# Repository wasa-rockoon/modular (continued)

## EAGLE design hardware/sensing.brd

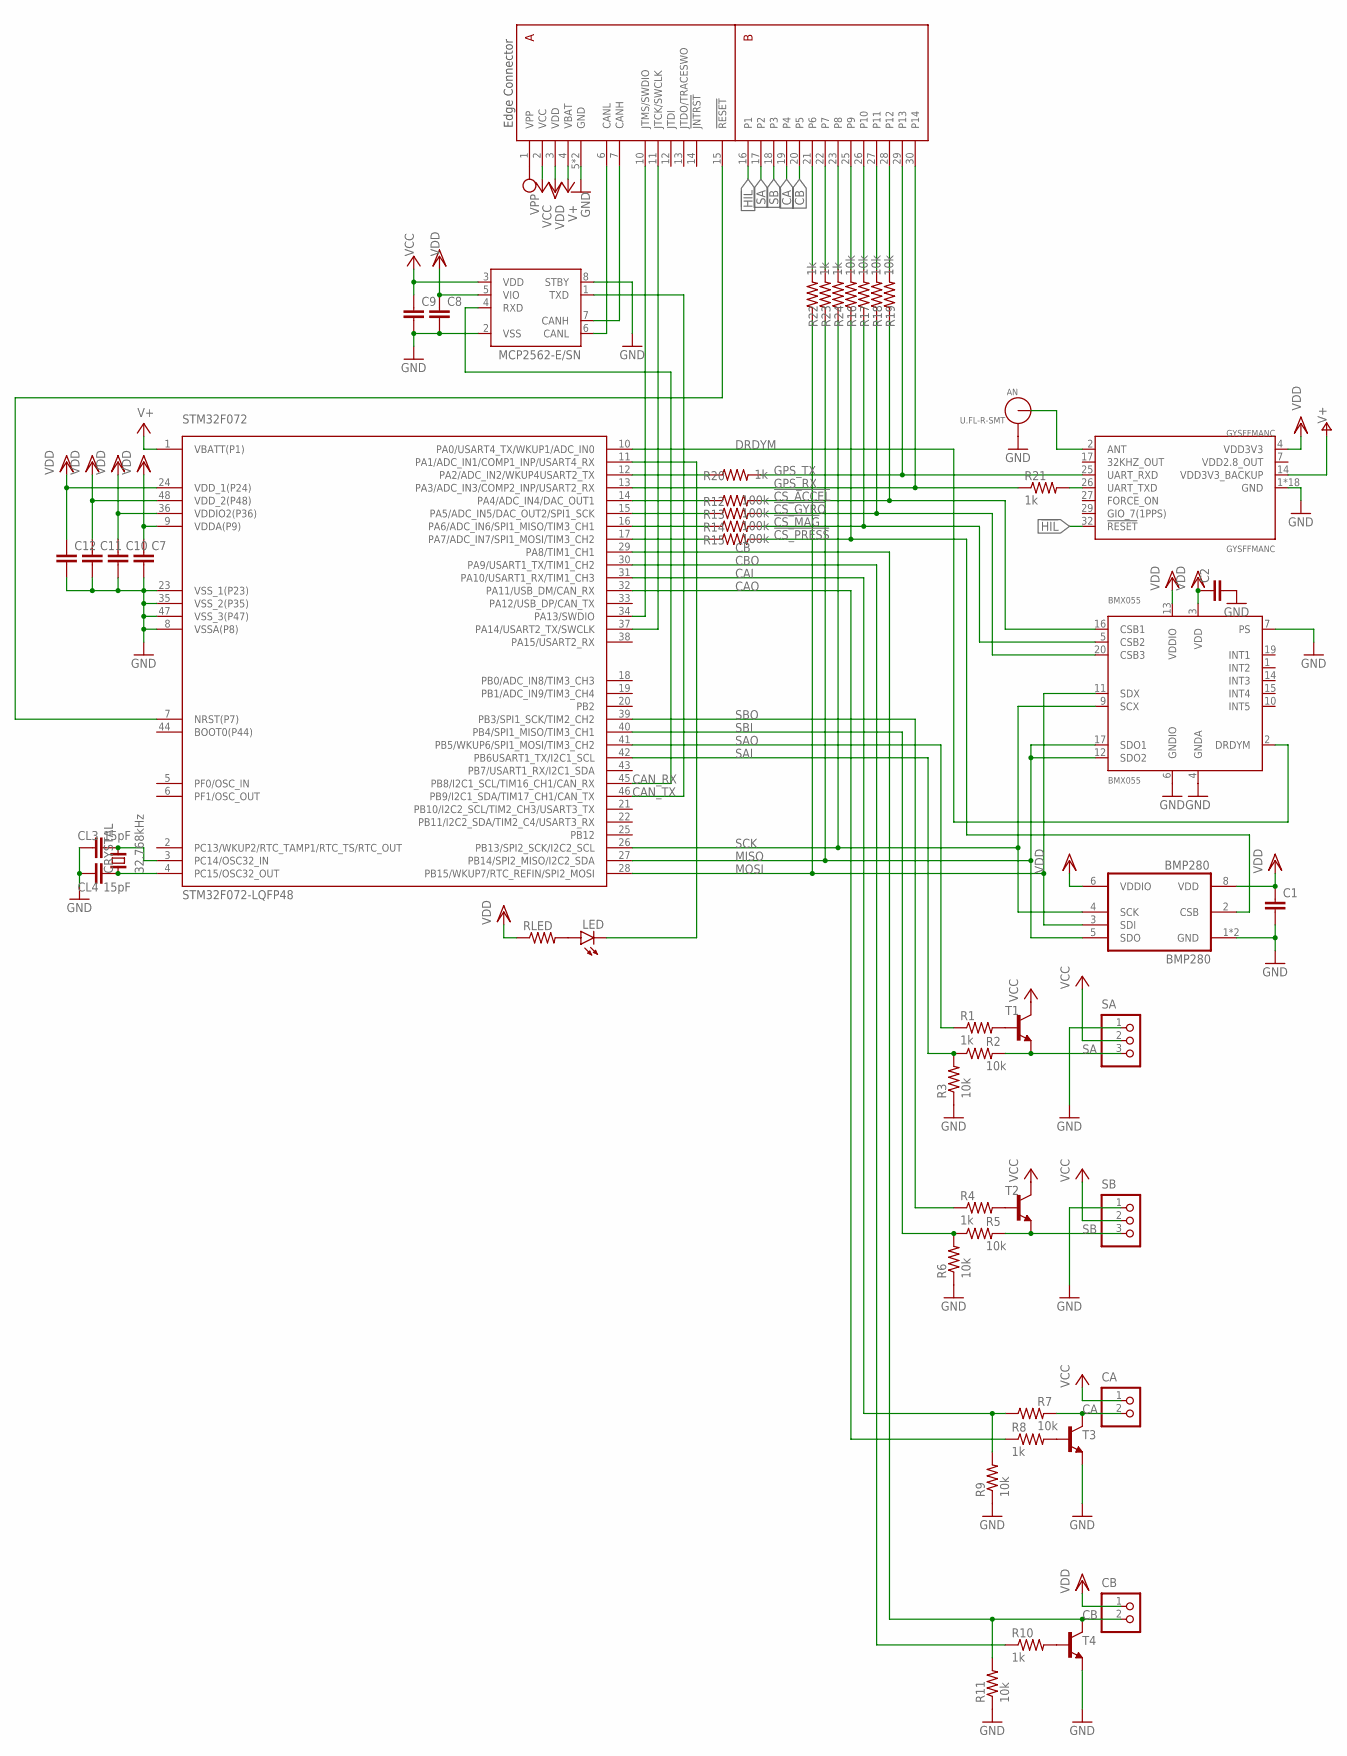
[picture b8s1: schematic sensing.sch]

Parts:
AN: U.FL-R-SMT; U.FL_SMT
BMP280: BMP280
BMX055: BMX055
C1, C2, C7, C8, C9, C10, C11, C12: C-EUC0603K; C0603K
CA: S2B-PH-K-S
CB: S2B-PH-K-S
CL3, CL4: 15pF; C0603K
CRYSTAL: 32.768kHz; FC-255
GYSFFMANC: GYSFFMANC
LED: LEDCHIP-LED0603; CHIP-LED0603
MCP2562: MCP2562-E/SN; SOIC127P600X175-8N
R1, R4, R8, R10, R20, R21, R22, R23, R24: 1k; R0603
R2, R3, R5, R6, R7, R9, R11, R16, R17, R18, R19: 10k; R0603
R12, R13, R14, R15: 100k; R0603
RLED: R-US_R0603; R0603
SA: S3B-PH-K-S
SB: S3B-PH-K-S
STM32F072: STM32F072-LQFP48; LQFP48
T1, T2, T3, T4: BC817-NPN-SOT23-BEC; SOT23-BEC
U$2: EDGE30

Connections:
!CS_ACCEL!: BMX055.16 (CSB1), R12.2, R19.1
!CS_GYRO!: BMX055.20 (CSB3), R13.2, R18.1
!CS_MAG!: BMX055.5 (CSB2), R14.2, R17.1
!CS_PRESS!: BMP280.2 (CSB), R15.2, R16.1
!HIL!: GYSFFMANC.32 (!RESET!), U$2.16 (P1)
CA: CA.2, R7.2, T3.C, U$2.19 (P4)
CAI: R7.1, R9.2, STM32F072.31 (PA10/USART1_RX/TIM1_CH3)
CANH1: MCP2562.7 (CANH), U$2.7 (CANH)
CANL1: MCP2562.6 (CANL), U$2.6 (CANL)
CAN_RX: MCP2562.4 (RXD), STM32F072.45 (PB8/I2C1_SCL/TIM16_CH1/CAN_RX)
CAN_TX: MCP2562.1 (TXD), STM32F072.46 (PB9/I2C1_SDA/TIM17_CH1/CAN_TX)
CAO: R8.1, STM32F072.32 (PA11/USB_DM/CAN_RX)
CB: CB.2, R11.2, STM32F072.29 (PA8/TIM1_CH1), T4.C, U$2.20 (P5)
CBO: R10.1, STM32F072.30 (PA9/USART1_TX/TIM1_CH2)
DRDYM: BMX055.2 (DRDYM), STM32F072.10 (PA0/USART4_TX/WKUP1/ADC_IN0)
GND: AN.GND1, AN.GND2, BMP280.1 (GND), BMP280.7 (GND), BMX055.4 (GNDA), BMX055.6 (GNDIO), BMX055.7 (PS), C1.2, C2.2, C7.2, C8.2, C9.2, C10.2, C11.2, C12.2, CL3.1, CL4.1, GYSFFMANC.1 (GND), GYSFFMANC.3 (GND), GYSFFMANC.8 (GND), GYSFFMANC.10 (GND), GYSFFMANC.12 (GND), GYSFFMANC.22 (GND), GYSFFMANC.33 (GND), GYSFFMANC.36 (GND), GYSFFMANC.37 (GND), GYSFFMANC.38 (GND), GYSFFMANC.39 (GND), GYSFFMANC.40 (GND), GYSFFMANC.41 (GND), GYSFFMANC.42 (GND), GYSFFMANC.43 (GND), GYSFFMANC.44 (GND), GYSFFMANC.45 (GND), GYSFFMANC.46 (GND), MCP2562.2 (VSS), MCP2562.8 (STBY), R3.1, R6.1, R9.1, R11.1, SA.1, SB.1, STM32F072.8 (VSSA(P8)), STM32F072.23 (VSS_1(P23)), STM32F072.35 (VSS_2(P35)), STM32F072.47 (VSS_3(P47)), T3.E, T4.E, U$2.5 (GND), U$2.8 (GND)
GPS_RX: R21.1, STM32F072.13 (PA3/ADC_IN3/COMP2_INP/USART2_RX), U$2.30 (P14)
GPS_TX: GYSFFMANC.25 (UART_RXD), R20.2, U$2.29 (P13)
MISO: BMP280.5 (SDO), BMX055.12 (SDO2), BMX055.17 (SDO1), R23.1, STM32F072.27 (PB14/SPI2_MISO/I2C2_SDA)
MOSI: BMP280.3 (SDI), BMX055.11 (SDX), R22.1, STM32F072.28 (PB15/WKUP7/RTC_REFIN/SPI2_MOSI)
unnamed: AN.SIG (ANT), GYSFFMANC.2 (ANT)
unnamed: R12.1, STM32F072.14 (PA4/ADC_IN4/DAC_OUT1)
unnamed: R1.2, T1.B
unnamed: R4.2, T2.B
unnamed: R13.1, STM32F072.15 (PA5/ADC_IN5/DAC_OUT2/SPI1_SCK)
unnamed: R14.1, STM32F072.16 (PA6/ADC_IN6/SPI1_MISO/TIM3_CH1)
unnamed: R15.1, STM32F072.17 (PA7/ADC_IN7/SPI1_MOSI/TIM3_CH2)
unnamed: R20.1, STM32F072.12 (PA2/ADC_IN2/WKUP4USART2_TX)
unnamed: GYSFFMANC.26 (UART_TXD), R21.2
unnamed: R8.2, T3.B
unnamed: R10.2, T4.B
unnamed: R24.2, U$2.23 (P8)
unnamed: R23.2, U$2.22 (P7)
unnamed: R22.2, U$2.21 (P6)
unnamed: R19.2, U$2.28 (P12)
unnamed: R18.2, U$2.27 (P11)
unnamed: R17.2, U$2.26 (P10)
unnamed: R16.2, U$2.25 (P9)
unnamed: LED.C, STM32F072.11 (PA1/ADC_IN1/COMP1_INP/USART4_RX)
unnamed: CL4.2, CRYSTAL.1, STM32F072.4 (PC15/OSC32_OUT)
unnamed: CL3.2, CRYSTAL.2, STM32F072.3 (PC14/OSC32_IN)
unnamed: LED.A, RLED.2
NRST1: STM32F072.7 (NRST(P7)), U$2.15 (!RESET!)
SA: R2.2, SA.3, T1.E, U$2.17 (P2)
SAI: R2.1, R3.2, STM32F072.42 (PB6USART1_TX/I2C1_SCL)
SAO: R1.1, STM32F072.41 (PB5/WKUP6/SPI1_MOSI/TIM3_CH2)
SB: R5.2, SB.3, T2.E, U$2.18 (P3)
SBI: R5.1, R6.2, STM32F072.40 (PB4/SPI1_MISO/TIM3_CH1)
SBO: R4.1, STM32F072.39 (PB3/SPI1_SCK/TIM2_CH2)
SCK: BMP280.4 (SCK), BMX055.9 (SCX), R24.1, STM32F072.26 (PB13/SPI2_SCK/I2C2_SCL)
SWCLK1: STM32F072.37 (PA14/USART2_TX/SWCLK), U$2.11 (JTCK/SWCLK)
SWDIO1: STM32F072.34 (PA13/SWDIO), U$2.10 (JTMS/SWDIO)
VBAT: GYSFFMANC.14 (VDD3V3_BACKUP), STM32F072.1 (VBATT(P1)), U$2.4 (VBAT)
VCC: C9.1, CA.1, MCP2562.3 (VDD), SA.2, SB.2, T1.C, T2.C, U$2.2 (VCC)
VDD: BMP280.6 (VDDIO), BMP280.8 (VDD), BMX055.3 (VDD), BMX055.13 (VDDIO), C1.1, C2.1, C7.1, C8.1, C10.1, C11.1, C12.1, CB.1, GYSFFMANC.4 (VDD3V3), MCP2562.5 (VIO), RLED.1, STM32F072.9 (VDDA(P9)), STM32F072.24 (VDD_1(P24)), STM32F072.36 (VDDIO2(P36)), STM32F072.48 (VDD_2(P48)), U$2.3 (VDD)
VDD2.8_OUT: GYSFFMANC.7 (VDD2.8_OUT)
VPP: U$2.1 (VPP)

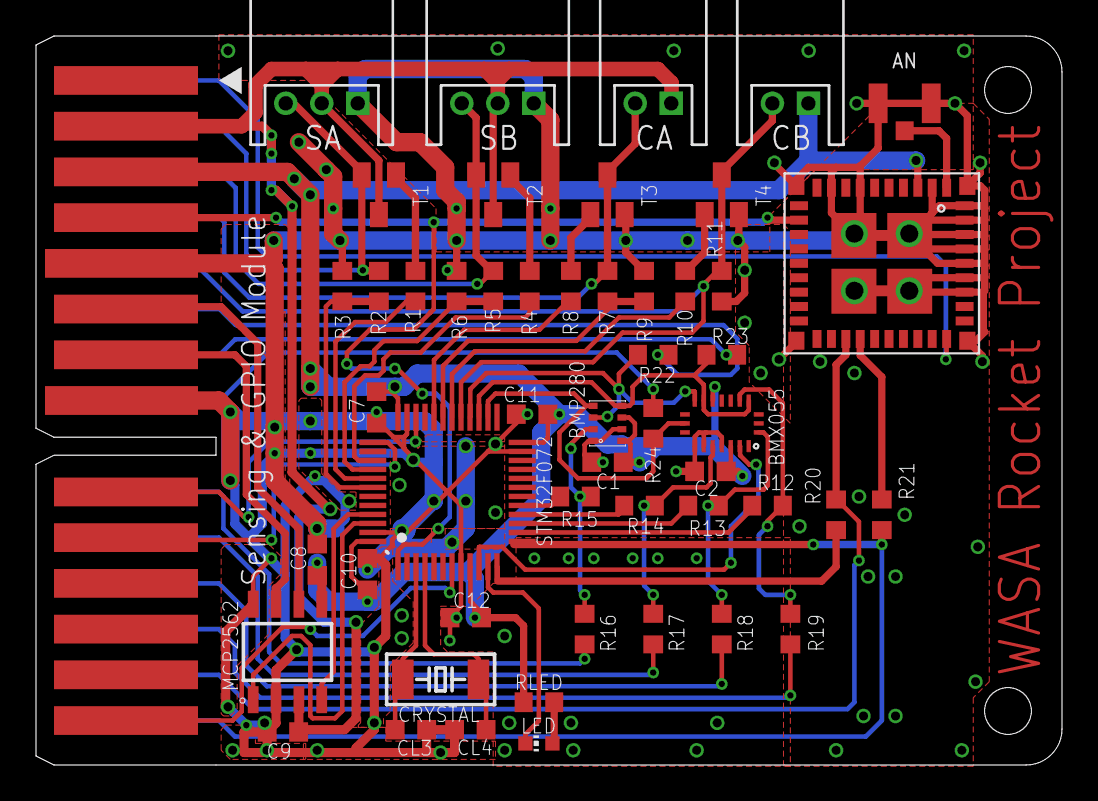
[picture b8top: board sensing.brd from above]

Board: 2 copper layers, 57.0 x 40.5 mm, 52 parts (0 on the bottom side), 55 nets.

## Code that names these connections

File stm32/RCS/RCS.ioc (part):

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Mcu.Name=STM32F042C(4-6)Tx
Mcu.Package=LQFP48
Mcu.UserName=STM32F042C6Tx
PA0.GPIOParameters=GPIO_Label
PA0.GPIO_Label=LED_ERROR
PA0.Signal=GPIO_Output
PA1.GPIOParameters=PinState,GPIO_PuPd,GPIO_Label,GPIO_ModeDefaultOutputPP
PA1.GPIO_Label=LED_A
PA1.GPIO_ModeDefaultOutputPP=GPIO_MODE_OUTPUT_PP
PA1.GPIO_PuPd=GPIO_NOPULL
PA1.PinState=GPIO_PIN_RESET
PA1.Signal=GPIO_Output
PA13.Mode=Serial_Wire
PA13.Signal=SYS_SWDIO
PA14.Mode=Serial_Wire
PA14.Signal=SYS_SWCLK
PA2.GPIOParameters=GPIO_Label
PA2.GPIO_Label=LED_B
PA2.Signal=GPIO_Output
PA3.GPIOParameters=GPIO_Label
PA3.GPIO_Label=LED_C
PA3.Signal=GPIO_Output
PA4.GPIOParameters=GPIO_Label
PA4.GPIO_Label=LED_D
PA4.Signal=S_TIM14_CH1
PA6.GPIOParameters=GPIO_Label
PA6.GPIO_Label=X_DATA
PA6.Signal=GPIO_Input
PA7.GPIOParameters=GPIO_Label
PA7.GPIO_Label=X_SCK
PA7.Signal=GPIO_Output
PA8.GPIOParameters=GPIO_Label
PA8.GPIO_Label=VALVE_A
PA8.Signal=GPIO_Output
PB0.GPIOParameters=GPIO_Label
PB0.GPIO_Label=PRESSURE
PB0.Mode=IN8
PB0.Signal=ADC_IN8
PB1.GPIOParameters=GPIO_Label
PB1.GPIO_Label=POWER_FB
PB1.Mode=IN9
PB1.Signal=ADC_IN9
PB10.GPIOParameters=GPIO_Label
PB10.GPIO_Label=Y_DATA
PB10.Signal=GPIO_Input
PB11.GPIOParameters=GPIO_Label
PB11.GPIO_Label=Y_SCK
PB11.Signal=GPIO_Output
PB12.GPIOParameters=GPIO_Label
PB12.GPIO_Label=POWER_ON
PB12.Signal=GPIO_Output
PB13.GPIOParameters=GPIO_Label
PB13.GPIO_Label=VALVE_D
PB13.Signal=GPIO_Output
PB14.GPIOParameters=GPIO_Label
PB14.GPIO_Label=VALVE_C
PB14.Signal=GPIO_Output
PB15.GPIOParameters=GPIO_Label
PB15.GPIO_Label=VALVE_B
PB15.Signal=GPIO_Output
PB8.GPIOParameters=GPIO_PuPd
PB8.GPIO_PuPd=GPIO_PULLUP
PB8.Mode=CAN_Activate
PB8.Signal=CAN_RX
PB9.Mode=CAN_Activate
PB9.Signal=CAN_TX
board=custom

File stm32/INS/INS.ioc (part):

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Mcu.Name=STM32L431C(B-C)Tx
Mcu.Package=LQFP48
Mcu.UserName=STM32L431CCTx
PA0.GPIOParameters=GPIO_Label
PA0.GPIO_Label=LED_ERROR
PA0.Signal=GPIO_Output
PA1.GPIOParameters=GPIO_Label
PA1.GPIO_Label=LED_STATUS
PA1.Signal=GPIO_Output
PA10.GPIOParameters=GPIO_Label
PA10.GPIO_Label=GPS_RX
PA10.Mode=Asynchronous
PA10.Signal=USART1_RX
PA11.GPIOParameters=GPIO_Label
PA11.GPIO_Label=TEMP_LOW
PA11.Signal=GPIO_Output
PA12.GPIOParameters=GPIO_Label
PA12.GPIO_Label=TEMP_HIGH
PA12.Signal=GPIO_Output
PA13\ (JTMS-SWDIO).Signal=SYS_JTMS-SWDIO
PA14\ (JTCK-SWCLK).Signal=SYS_JTCK-SWCLK
PA2.Mode=Asynchronous
PA2.Signal=USART2_TX
PA3.Mode=Asynchronous
PA3.Signal=USART2_RX
PA8.GPIOParameters=GPIO_Label
PA8.GPIO_Label=GPS_RESET
PA8.Signal=GPIO_Output
PA9.GPIOParameters=GPIO_Label
PA9.GPIO_Label=GPS_TX
PA9.Mode=Asynchronous
PA9.Signal=USART1_TX
PB1.GPIOParameters=GPIO_Label
PB1.GPIO_Label=TEMP
PB1.Signal=ADCx_IN16
PB10.Mode=I2C
PB10.Signal=I2C2_SCL
PB11.Mode=I2C
PB11.Signal=I2C2_SDA
PB15.GPIOParameters=GPIO_Label
PB15.GPIO_Label=GPS_1PPS
PB15.Signal=GPIO_Input
PB2.GPIOParameters=GPIO_Label
PB2.GPIO_Label=BNO_RESET
PB2.Signal=GPIO_Output
PB6.Mode=I2C
PB6.Signal=I2C1_SCL
PB7.Mode=I2C
PB7.Signal=I2C1_SDA
PB8.Mode=CAN_Activate
PB8.Signal=CAN1_RX
PB9.Mode=CAN_Activate
PB9.Signal=CAN1_TX
PC14-OSC32_IN\ (PC14).Mode=LSE-External-Oscillator
PC14-OSC32_IN\ (PC14).Signal=RCC_OSC32_IN
PC15-OSC32_OUT\ (PC15).Mode=LSE-External-Oscillator
PC15-OSC32_OUT\ (PC15).Signal=RCC_OSC32_OUT
RCC.HSE_VALUE=8000000
RCC.SYSCLKFreq_VALUE=80000000
RCC.SYSCLKSource=RCC_SYSCLKSOURCE_PLLCLK
board=custom

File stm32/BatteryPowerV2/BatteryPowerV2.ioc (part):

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Mcu.Name=STM32F042C(4-6)Tx
Mcu.Package=LQFP48
Mcu.UserName=STM32F042C6Tx
PA0.GPIOParameters=GPIO_Label
PA0.GPIO_Label=LED_ERROR
PA0.Signal=GPIO_Output
PA1.GPIOParameters=GPIO_Label
PA1.GPIO_Label=LED_STATUS
PA1.Signal=GPIO_Output
PA10.GPIOParameters=GPIO_Label
PA10.GPIO_Label=SUPPLY_CON
PA10.Signal=GPIO_Input
PA11.GPIOParameters=GPIO_Label
PA11.GPIO_Label=SUPPLY_3V3
PA11.Signal=GPIO_Output
PA12.GPIOParameters=GPIO_Label
PA12.GPIO_Label=SUPPLY_5V
PA12.Signal=GPIO_Output
PA13.Mode=Serial_Wire
PA13.Signal=SYS_SWDIO
PA14.Mode=Serial_Wire
PA14.Signal=SYS_SWCLK
PA2.GPIOParameters=GPIO_Label
PA2.GPIO_Label=TEMP
PA2.Mode=IN2
PA2.Signal=ADC_IN2
PA3.GPIOParameters=GPIO_Label
PA3.GPIO_Label=VDD_V
PA3.Mode=IN3
PA3.Signal=ADC_IN3
PA4.GPIOParameters=GPIO_Label
PA4.GPIO_Label=VDD_I
PA4.Mode=IN4
PA4.Signal=ADC_IN4
PA5.GPIOParameters=GPIO_Label
PA5.GPIO_Label=VCC_V
PA5.Mode=IN5
PA5.Signal=ADC_IN5
PA6.GPIOParameters=GPIO_Label
PA6.GPIO_Label=VCC_I
PA6.Mode=IN6
PA6.Signal=ADC_IN6
PA7.GPIOParameters=GPIO_Label
PA7.GPIO_Label=BAT2_V
PA7.Mode=IN7
PA7.Signal=ADC_IN7
PA9.GPIOParameters=GPIO_Label
PA9.GPIO_Label=HEATER
PA9.Signal=GPIO_Output
PB0.GPIOParameters=GPIO_Label
PB0.GPIO_Label=BAT1_V
PB0.Mode=IN8
PB0.Signal=ADC_IN8
PB1.GPIOParameters=GPIO_Label
PB1.GPIO_Label=VPP_V
PB1.Mode=IN9
PB1.Signal=ADC_IN9
PB8.Mode=CAN_Activate
PB8.Signal=CAN_RX
PB9.Mode=CAN_Activate
PB9.Signal=CAN_TX
PC14OSC32_IN.Mode=LSE-External-Oscillator
PC14OSC32_IN.Signal=RCC_OSC32_IN
PC15OSC32_OUT.Mode=LSE-External-Oscillator
PC15OSC32_OUT.Signal=RCC_OSC32_OUT
RCC.SYSCLKFreq_VALUE=48000000
RCC.SYSCLKSource=RCC_SYSCLKSOURCE_HSI48
board=custom

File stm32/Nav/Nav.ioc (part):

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Mcu.Name=STM32G431C(6-8-B)Tx
Mcu.Package=LQFP48
Mcu.UserName=STM32G431C6Tx
PA0.GPIOParameters=GPIO_Label
PA0.GPIO_Label=DRDYM
PA0.Signal=GPIO_Input
PA1.GPIOParameters=PinState,GPIO_Label
PA1.GPIO_Label=LED
PA1.PinState=GPIO_PIN_SET
PA1.Signal=GPIO_Output
PA11.GPIOParameters=GPIO_Label
PA11.GPIO_Label=CAN_RX
PA11.Mode=FDCAN_Activate
PA11.Signal=FDCAN1_RX
PA12.GPIOParameters=GPIO_Label
PA12.GPIO_Label=CAN_TX
PA12.Mode=FDCAN_Activate
PA12.Signal=FDCAN1_TX
PA13.Mode=Serial_Wire
PA13.Signal=SYS_JTMS-SWDIO
PA14.Mode=Serial_Wire
PA14.Signal=SYS_JTCK-SWCLK
PA2.GPIOParameters=GPIO_Label
PA2.GPIO_Label=GPS_TX
PA2.Mode=Asynchronous
PA2.Signal=USART2_TX
PA3.GPIOParameters=GPIO_Label
PA3.GPIO_Label=GPS_RX
PA3.Mode=Asynchronous
PA3.Signal=USART2_RX
PA4.GPIOParameters=GPIO_Speed,PinState,GPIO_Label
PA4.GPIO_Label=CS_ACCL
PA4.GPIO_Speed=GPIO_SPEED_FREQ_HIGH
PA4.PinState=GPIO_PIN_SET
PA4.Signal=GPIO_Output
PA5.GPIOParameters=GPIO_Speed,PinState,GPIO_Label
PA5.GPIO_Label=CS_MAG
PA5.GPIO_Speed=GPIO_SPEED_FREQ_HIGH
PA5.PinState=GPIO_PIN_SET
PA5.Signal=GPIO_Output
PA6.GPIOParameters=GPIO_Speed,PinState,GPIO_Label
PA6.GPIO_Label=CS_GYRO
PA6.GPIO_Speed=GPIO_SPEED_FREQ_HIGH
PA6.PinState=GPIO_PIN_SET
PA6.Signal=GPIO_Output
PA7.GPIOParameters=GPIO_Speed,PinState,GPIO_Label
PA7.GPIO_Label=CS_PRES
PA7.GPIO_Speed=GPIO_SPEED_FREQ_HIGH
PA7.PinState=GPIO_PIN_SET
PA7.Signal=GPIO_Output
PA8.GPIOParameters=GPIO_Label
PA8.GPIO_Label=I2C_SDA
PA8.Mode=I2C
PA8.Signal=I2C2_SDA
PA9.GPIOParameters=GPIO_Label
PA9.GPIO_Label=I2C_SCL
PA9.Mode=I2C
PA9.Signal=I2C2_SCL
PB13.GPIOParameters=GPIO_Speed,GPIO_Label
PB13.GPIO_Label=SPI_SCK
PB13.GPIO_Speed=GPIO_SPEED_FREQ_HIGH
PB13.Mode=Full_Duplex_Master
PB13.Signal=SPI2_SCK
PB14.GPIOParameters=GPIO_Speed,GPIO_Label
PB14.GPIO_Label=SPI_MISO
PB14.GPIO_Speed=GPIO_SPEED_FREQ_HIGH
PB14.Mode=Full_Duplex_Master
PB14.Signal=SPI2_MISO
PB15.GPIOParameters=GPIO_Speed,GPIO_Label
PB15.GPIO_Label=SPI_MOSI
PB15.GPIO_Speed=GPIO_SPEED_FREQ_HIGH
PB15.Mode=Full_Duplex_Master
PB15.Signal=SPI2_MOSI
RCC.HSE_VALUE=8000000
RCC.SYSCLKFreq_VALUE=150000000
RCC.SYSCLKSource=RCC_SYSCLKSOURCE_PLLCLK
board=custom

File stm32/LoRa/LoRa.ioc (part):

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Mcu.Name=STM32F042C(4-6)Tx
Mcu.Package=LQFP48
Mcu.UserName=STM32F042C6Tx
PA0.GPIOParameters=GPIO_Label
PA0.GPIO_Label=LED_ERROR
PA0.Signal=GPIO_Output
PA1.GPIOParameters=GPIO_Label
PA1.GPIO_Label=LED_STATUS1
PA1.Signal=GPIO_Output
PA10.GPIOParameters=GPIO_ModeDefaultPP,GPIO_Speed,GPIO_PuPd
PA10.GPIO_ModeDefaultPP=GPIO_MODE_AF_PP
PA10.GPIO_PuPd=GPIO_NOPULL
PA10.GPIO_Speed=GPIO_SPEED_FREQ_HIGH
PA10.Mode=Asynchronous
PA10.Signal=USART1_RX
PA11.GPIOParameters=GPIO_Label
PA11.GPIO_Label=LORA1_M1
PA11.Signal=GPIO_Output
PA12.GPIOParameters=GPIO_Label
PA12.GPIO_Label=LORA1_M0
PA12.Signal=GPIO_Output
PA13.Mode=Serial_Wire
PA13.Signal=SYS_SWDIO
PA14.Mode=Serial_Wire
PA14.Signal=SYS_SWCLK
PA2.GPIOParameters=GPIO_ModeDefaultPP,GPIO_Speed,GPIO_PuPd
PA2.GPIO_ModeDefaultPP=GPIO_MODE_AF_PP
PA2.GPIO_PuPd=GPIO_NOPULL
PA2.GPIO_Speed=GPIO_SPEED_FREQ_HIGH
PA2.Mode=Asynchronous
PA2.Signal=USART2_TX
PA3.GPIOParameters=GPIO_ModeDefaultPP,GPIO_Speed,GPIO_PuPd
PA3.GPIO_ModeDefaultPP=GPIO_MODE_AF_PP
PA3.GPIO_PuPd=GPIO_NOPULL
PA3.GPIO_Speed=GPIO_SPEED_FREQ_HIGH
PA3.Mode=Asynchronous
PA3.Signal=USART2_RX
PA4.GPIOParameters=GPIO_Label
PA4.GPIO_Label=LED_STATUS2
PA4.Signal=GPIO_Output
PA5.GPIOParameters=GPIO_PuPd,GPIO_Label
PA5.GPIO_Label=LORA2_AUX
PA5.GPIO_PuPd=GPIO_PULLUP
PA5.Signal=GPIO_Input
PA6.GPIOParameters=GPIO_Label
PA6.GPIO_Label=LORA2_M1
PA6.Signal=GPIO_Output
PA7.GPIOParameters=GPIO_Label
PA7.GPIO_Label=LORA2_M0
PA7.Signal=GPIO_Output
PA9.GPIOParameters=GPIO_ModeDefaultPP,GPIO_Speed,GPIO_PuPd
PA9.GPIO_ModeDefaultPP=GPIO_MODE_AF_PP
PA9.GPIO_PuPd=GPIO_NOPULL
PA9.GPIO_Speed=GPIO_SPEED_FREQ_HIGH
PA9.Mode=Asynchronous
PA9.Signal=USART1_TX
PB11.GPIOParameters=GPIO_PuPd,GPIO_Label
PB11.GPIO_Label=LORA1_AUX
PB11.GPIO_PuPd=GPIO_PULLUP
PB11.Signal=GPIO_Input
PB8.GPIOParameters=GPIO_PuPd
PB8.GPIO_PuPd=GPIO_PULLUP
PB8.Mode=CAN_Activate
PB8.Signal=CAN_RX
PB9.Mode=CAN_Activate
PB9.Signal=CAN_TX
PC14OSC32_IN.Mode=LSE-External-Oscillator
PC14OSC32_IN.Signal=RCC_OSC32_IN
PC15OSC32_OUT.Mode=LSE-External-Oscillator
PC15OSC32_OUT.Signal=RCC_OSC32_OUT
RCC.SYSCLKFreq_VALUE=48000000
RCC.SYSCLKSource=RCC_SYSCLKSOURCE_HSI48
board=custom

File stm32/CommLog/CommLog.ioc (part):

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Mcu.Name=STM32F042C(4-6)Tx
Mcu.Package=LQFP48
Mcu.UserName=STM32F042C6Tx
PA1.GPIOParameters=GPIO_Label
PA1.GPIO_Label=LED
PA1.Signal=GPIO_Output
PA11.GPIOParameters=PinState,GPIO_PuPd,GPIO_Label,GPIO_ModeDefaultOutputPP
PA11.GPIO_Label=TWE_NRST
PA11.GPIO_ModeDefaultOutputPP=GPIO_MODE_OUTPUT_OD
PA11.GPIO_PuPd=GPIO_PULLUP
PA11.PinState=GPIO_PIN_SET
PA11.Signal=GPIO_Output
PA13.Mode=Serial_Wire
PA13.Signal=SYS_SWDIO
PA14.Mode=Serial_Wire
PA14.Signal=SYS_SWCLK
PA15.GPIOParameters=GPIO_ModeDefaultPP,GPIO_PuPd,GPIO_Label
PA15.GPIO_Label=LORA_RTX
PA15.GPIO_ModeDefaultPP=GPIO_MODE_AF_OD
PA15.GPIO_PuPd=GPIO_PULLUP
PA15.Mode=Asynchronous
PA15.Signal=USART2_RX
PA2.GPIOParameters=GPIO_ModeDefaultPP,GPIO_PuPd,GPIO_Label
PA2.GPIO_Label=LORA_TRX
PA2.GPIO_ModeDefaultPP=GPIO_MODE_AF_OD
PA2.GPIO_PuPd=GPIO_PULLUP
PA2.Mode=Asynchronous
PA2.Signal=USART2_TX
PA3.GPIOParameters=GPIO_PuPd,GPIO_Label
PA3.GPIO_Label=SD_NSW
PA3.GPIO_PuPd=GPIO_PULLUP
PA3.Signal=GPIO_Input
PA8.GPIOParameters=PinState,GPIO_PuPd,GPIO_Label,GPIO_ModeDefaultOutputPP
PA8.GPIO_Label=LORA_NSLEEP
PA8.GPIO_ModeDefaultOutputPP=GPIO_MODE_OUTPUT_OD
PA8.GPIO_PuPd=GPIO_PULLUP
PA8.PinState=GPIO_PIN_SET
PA8.Signal=GPIO_Output
PB13.GPIOParameters=GPIO_Label
PB13.GPIO_Label=SD_SCK
PB13.Mode=Full_Duplex_Master
PB13.Signal=SPI2_SCK
PB14.GPIOParameters=GPIO_PuPd,GPIO_Label
PB14.GPIO_Label=SD_MISO
PB14.GPIO_PuPd=GPIO_PULLUP
PB14.Mode=Full_Duplex_Master
PB14.Signal=SPI2_MISO
PB15.GPIOParameters=GPIO_PuPd,GPIO_Label
PB15.GPIO_Label=SD_MOSI
PB15.GPIO_PuPd=GPIO_PULLUP
PB15.Mode=Full_Duplex_Master
PB15.Signal=SPI2_MOSI
PB3.GPIOParameters=PinState,GPIO_PuPd,GPIO_Label,GPIO_ModeDefaultOutputPP
PB3.GPIO_Label=TWE_NSLEEP
PB3.GPIO_ModeDefaultOutputPP=GPIO_MODE_OUTPUT_OD
PB3.GPIO_PuPd=GPIO_PULLUP
PB3.PinState=GPIO_PIN_SET
PB3.Signal=GPIO_Output
PB4.GPIOParameters=PinState,GPIO_PuPd,GPIO_Label,GPIO_ModeDefaultOutputPP
PB4.GPIO_Label=TWE_NPGM
PB4.GPIO_ModeDefaultOutputPP=GPIO_MODE_OUTPUT_OD
PB4.GPIO_PuPd=GPIO_PULLUP
PB4.PinState=GPIO_PIN_SET
PB4.Signal=GPIO_Output
PB6.GPIOParameters=GPIO_ModeDefaultPP,GPIO_PuPd,GPIO_Label
PB6.GPIO_Label=TWE_TRX
PB6.GPIO_ModeDefaultPP=GPIO_MODE_AF_OD
PB6.GPIO_PuPd=GPIO_PULLUP
PB6.Mode=Asynchronous
PB6.Signal=USART1_TX
PB7.GPIOParameters=GPIO_ModeDefaultPP,GPIO_PuPd,GPIO_Label
PB7.GPIO_Label=TWE_RTX
PB7.GPIO_ModeDefaultPP=GPIO_MODE_AF_OD
PB7.GPIO_PuPd=GPIO_PULLUP
PB7.Mode=Asynchronous
PB7.Signal=USART1_RX
PB8.GPIOParameters=GPIO_PuPd
PB8.GPIO_PuPd=GPIO_PULLUP
PB8.Mode=CAN_Activate
PB8.Signal=CAN_RX
PB9.Mode=CAN_Activate
PB9.Signal=CAN_TX
PC13.GPIOParameters=PinState,GPIO_PuPd,GPIO_Label,GPIO_ModeDefaultOutputPP
PC13.GPIO_Label=LORA_NRST
PC13.GPIO_ModeDefaultOutputPP=GPIO_MODE_OUTPUT_OD
PC13.GPIO_PuPd=GPIO_PULLUP
PC13.PinState=GPIO_PIN_SET
PC13.Signal=GPIO_Output
RCC.SYSCLKFreq_VALUE=48000000
RCC.SYSCLKSource=RCC_SYSCLKSOURCE_HSI48
board=custom

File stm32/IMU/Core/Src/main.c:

/* USER CODE BEGIN Header */
/**
  ******************************************************************************
  * @file           : main.c
  * @brief          : Main program body
  ******************************************************************************
  * @attention
  *
  * Copyright (c) 2022 STMicroelectronics.
  * All rights reserved.
  *
  * This software is licensed under terms that can be found in the LICENSE file
  * in the root directory of this software component.
  * If no LICENSE file comes with this software, it is provided AS-IS.
  *
  ******************************************************************************
  */
/* USER CODE END Header */
/* Includes ------------------------------------------------------------------*/
#include "main.h"

/* Private includes ----------------------------------------------------------*/
/* USER CODE BEGIN Includes */

/* USER CODE END Includes */

/* Private typedef -----------------------------------------------------------*/
/* USER CODE BEGIN PTD */

/* USER CODE END PTD */

/* Private define ------------------------------------------------------------*/
/* USER CODE BEGIN PD */
/* USER CODE END PD */

/* Private macro -------------------------------------------------------------*/
/* USER CODE BEGIN PM */

/* USER CODE END PM */

/* Private variables ---------------------------------------------------------*/
 CAN_HandleTypeDef hcan;

SPI_HandleTypeDef hspi2;

UART_HandleTypeDef huart2;

/* USER CODE BEGIN PV */

/* USER CODE END PV */

/* Private function prototypes -----------------------------------------------*/
void SystemClock_Config(void);
static void MX_GPIO_Init(void);
static void MX_CAN_Init(void);
static void MX_SPI2_Init(void);
static void MX_USART2_UART_Init(void);
/* USER CODE BEGIN PFP */

/* USER CODE END PFP */

/* Private user code ---------------------------------------------------------*/
/* USER CODE BEGIN 0 */

/* USER CODE END 0 */

/**
  * @brief  The application entry point.
  * @retval int
  */
int main(void)
{
  /* USER CODE BEGIN 1 */

  /* USER CODE END 1 */

  /* MCU Configuration--------------------------------------------------------*/

  /* Reset of all peripherals, Initializes the Flash interface and the Systick. */
  HAL_Init();

  /* USER CODE BEGIN Init */

  /* USER CODE END Init */

  /* Configure the system clock */
  SystemClock_Config();

  /* USER CODE BEGIN SysInit */

  /* USER CODE END SysInit */

  /* Initialize all configured peripherals */
  MX_GPIO_Init();
  MX_CAN_Init();
  MX_SPI2_Init();
  MX_USART2_UART_Init();
  /* USER CODE BEGIN 2 */

  /* USER CODE END 2 */

  /* Infinite loop */
  /* USER CODE BEGIN WHILE */
  while (1)
  {
    /* USER CODE END WHILE */

    /* USER CODE BEGIN 3 */
  }
  /* USER CODE END 3 */
}

/**
  * @brief System Clock Configuration
  * @retval None
  */
void SystemClock_Config(void)
{
  RCC_OscInitTypeDef RCC_OscInitStruct = {0};
  RCC_ClkInitTypeDef RCC_ClkInitStruct = {0};

  /** Initializes the RCC Oscillators according to the specified parameters
  * in the RCC_OscInitTypeDef structure.
  */
  RCC_OscInitStruct.OscillatorType = RCC_OSCILLATORTYPE_HSI48;
  RCC_OscInitStruct.HSI48State = RCC_HSI48_ON;
  RCC_OscInitStruct.PLL.PLLState = RCC_PLL_NONE;
  if (HAL_RCC_OscConfig(&RCC_OscInitStruct) != HAL_OK)
  {
    Error_Handler();
  }

  /** Initializes the CPU, AHB and APB buses clocks
  */
  RCC_ClkInitStruct.ClockType = RCC_CLOCKTYPE_HCLK|RCC_CLOCKTYPE_SYSCLK
                              |RCC_CLOCKTYPE_PCLK1;
  RCC_ClkInitStruct.SYSCLKSource = RCC_SYSCLKSOURCE_HSI48;
  RCC_ClkInitStruct.AHBCLKDivider = RCC_SYSCLK_DIV1;
  RCC_ClkInitStruct.APB1CLKDivider = RCC_HCLK_DIV1;

  if (HAL_RCC_ClockConfig(&RCC_ClkInitStruct, FLASH_LATENCY_1) != HAL_OK)
  {
    Error_Handler();
  }
}

/**
  * @brief CAN Initialization Function
  * @param None
  * @retval None
  */
static void MX_CAN_Init(void)
{

  /* USER CODE BEGIN CAN_Init 0 */

  /* USER CODE END CAN_Init 0 */

  /* USER CODE BEGIN CAN_Init 1 */

  /* USER CODE END CAN_Init 1 */
  hcan.Instance = CAN;
  hcan.Init.Prescaler = 24;
  hcan.Init.Mode = CAN_MODE_NORMAL;
  hcan.Init.SyncJumpWidth = CAN_SJW_1TQ;
  hcan.Init.TimeSeg1 = CAN_BS1_12TQ;
  hcan.Init.TimeSeg2 = CAN_BS2_3TQ;
  hcan.Init.TimeTriggeredMode = DISABLE;
  hcan.Init.AutoBusOff = DISABLE;
  hcan.Init.AutoWakeUp = DISABLE;
  hcan.Init.AutoRetransmission = DISABLE;
  hcan.Init.ReceiveFifoLocked = DISABLE;
  hcan.Init.TransmitFifoPriority = DISABLE;
  if (HAL_CAN_Init(&hcan) != HAL_OK)
  {
    Error_Handler();
  }
  /* USER CODE BEGIN CAN_Init 2 */

  /* USER CODE END CAN_Init 2 */

}

/**
  * @brief SPI2 Initialization Function
  * @param None
  * @retval None
  */
static void MX_SPI2_Init(void)
{

  /* USER CODE BEGIN SPI2_Init 0 */

  /* USER CODE END SPI2_Init 0 */

  /* USER CODE BEGIN SPI2_Init 1 */

  /* USER CODE END SPI2_Init 1 */
  /* SPI2 parameter configuration*/
  hspi2.Instance = SPI2;
  hspi2.Init.Mode = SPI_MODE_MASTER;
  hspi2.Init.Direction = SPI_DIRECTION_2LINES;
  hspi2.Init.DataSize = SPI_DATASIZE_8BIT;
  hspi2.Init.CLKPolarity = SPI_POLARITY_HIGH;
  hspi2.Init.CLKPhase = SPI_PHASE_2EDGE;
  hspi2.Init.NSS = SPI_NSS_SOFT;
  hspi2.Init.BaudRatePrescaler = SPI_BAUDRATEPRESCALER_8;
  hspi2.Init.FirstBit = SPI_FIRSTBIT_MSB;
  hspi2.Init.TIMode = SPI_TIMODE_DISABLE;
  hspi2.Init.CRCCalculation = SPI_CRCCALCULATION_DISABLE;
  hspi2.Init.CRCPolynomial = 7;
  hspi2.Init.CRCLength = SPI_CRC_LENGTH_DATASIZE;
  hspi2.Init.NSSPMode = SPI_NSS_PULSE_DISABLE;
  if (HAL_SPI_Init(&hspi2) != HAL_OK)
  {
    Error_Handler();
  }
  /* USER CODE BEGIN SPI2_Init 2 */

  /* USER CODE END SPI2_Init 2 */

}

/**
  * @brief USART2 Initialization Function
  * @param None
  * @retval None
  */
static void MX_USART2_UART_Init(void)
{

  /* USER CODE BEGIN USART2_Init 0 */

  /* USER CODE END USART2_Init 0 */

  /* USER CODE BEGIN USART2_Init 1 */

  /* USER CODE END USART2_Init 1 */
  huart2.Instance = USART2;
  huart2.Init.BaudRate = 9600;
  huart2.Init.WordLength = UART_WORDLENGTH_8B;
  huart2.Init.StopBits = UART_STOPBITS_1;
  huart2.Init.Parity = UART_PARITY_NONE;
  huart2.Init.Mode = UART_MODE_TX_RX;
  huart2.Init.HwFlowCtl = UART_HWCONTROL_NONE;
  huart2.Init.OverSampling = UART_OVERSAMPLING_16;
  huart2.Init.OneBitSampling = UART_ONE_BIT_SAMPLE_DISABLE;
  huart2.AdvancedInit.AdvFeatureInit = UART_ADVFEATURE_NO_INIT;
  if (HAL_UART_Init(&huart2) != HAL_OK)
  {
    Error_Handler();
  }
  /* USER CODE BEGIN USART2_Init 2 */

  /* USER CODE END USART2_Init 2 */

}

/**
  * @brief GPIO Initialization Function
  * @param None
  * @retval None
  */
static void MX_GPIO_Init(void)
{
  GPIO_InitTypeDef GPIO_InitStruct = {0};

  /* GPIO Ports Clock Enable */
  __HAL_RCC_GPIOA_CLK_ENABLE();
  __HAL_RCC_GPIOB_CLK_ENABLE();

  /*Configure GPIO pin Output Level */
  HAL_GPIO_WritePin(LED_GPIO_Port, LED_Pin, GPIO_PIN_RESET);

  /*Configure GPIO pin Output Level */
  HAL_GPIO_WritePin(GPIOA, CS_ACCEL_Pin|CS_MAG_Pin|CS_GYRO_Pin|CS_PRESS_Pin, GPIO_PIN_SET);

  /*Configure GPIO pins : LED_Pin CS_ACCEL_Pin CS_MAG_Pin CS_GYRO_Pin
                           CS_PRESS_Pin */
  GPIO_InitStruct.Pin = LED_Pin|CS_ACCEL_Pin|CS_MAG_Pin|CS_GYRO_Pin
                          |CS_PRESS_Pin;
  GPIO_InitStruct.Mode = GPIO_MODE_OUTPUT_PP;
  GPIO_InitStruct.Pull = GPIO_NOPULL;
  GPIO_InitStruct.Speed = GPIO_SPEED_FREQ_LOW;
  HAL_GPIO_Init(GPIOA, &GPIO_InitStruct);

}

/* USER CODE BEGIN 4 */

/* USER CODE END 4 */

/**
  * @brief  This function is executed in case of error occurrence.
  * @retval None
  */
void Error_Handler(void)
{
  /* USER CODE BEGIN Error_Handler_Debug */
  /* User can add his own implementation to report the HAL error return state */
  __disable_irq();
  while (1)
  {
  }
  /* USER CODE END Error_Handler_Debug */
}

#ifdef  USE_FULL_ASSERT
/**
  * @brief  Reports the name of the source file and the source line number
  *         where the assert_param error has occurred.
  * @param  file: pointer to the source file name
  * @param  line: assert_param error line source number
  * @retval None
  */
void assert_failed(uint8_t *file, uint32_t line)
{
  /* USER CODE BEGIN 6 */
  /* User can add his own implementation to report the file name and line number,
     ex: printf("Wrong parameters value: file %s on line %d\r\n", file, line) */
  /* USER CODE END 6 */
}
#endif /* USE_FULL_ASSERT */

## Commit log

2019-10-18 Create igniter driver
2019-10-18 Eagle project setting
2019-10-22 Module common part
2019-10-26 Add battery power board
2019-10-26 Add USB&LiPo power board
2019-10-26 Add igniter driver board
2019-11-01 Add communication and logging board
2019-11-02 Add base board
2019-11-05 Layout battery power board
2019-11-06 Layout and route base board
2019-11-07 Layout igniter driver board
2019-11-10 Layout USB and LiPo power board
2019-11-11 Add sensing and GPIO board
2019-11-11 Complete base board
2019-11-12 Complete USB & LiPo power board
2019-11-12 Complete battery power board
2019-11-12 Complete igniter driver board
2019-11-12 Complete communication & logging board
2019-11-13 Clean silk print
2020-05-11 Some fixes
2020-05-11 Add stm32 project of Comm&Log module
2020-05-11 Add stm32 project of BatteryPower module
2021-04-17 Add spin gantry launcher
2022-05-26 bland new command system
2022-06-23 Add BMX055
2022-06-26 Add pressure sensor, voltage and current sensing
2022-07-03 Add nav board
2022-07-03 Renew command system
2022-08-12 Update CAN command channel
2022-08-22 Add nav module
2022-08-22 Update command system
2022-08-22 Fix reset wire
2022-08-22 Add writing log to SD card
2022-08-22 unknown
2022-08-24 Add queue to command channel
2022-08-24 Add ground station lcd controller
2022-09-08 LoRa (WIP)
2022-09-08 Add GS server
2022-09-09 Update GS server
2022-09-10 Use sync web server (not working)
2022-09-11 Fix bug and add chart
2022-09-11 Change sampling rate
2022-09-12 Fix command decoding bug
2022-09-12 Update LoRa and command
2022-09-12 Add navigation module
2022-09-13 Add IMU module
2022-09-13 Add sensor module
2022-09-16 Add igniter module
2022-09-16 Add diagnostics
2022-09-18 Add showing launcher location
2022-09-21 Fix showing location
2023-05-07 新モジュール回路設計完了
2023-05-24 LoRaモジュール、基板設計完了です。
2023-05-25 BatteryPowerV2とINSの基板設計です。変えたつもりはないんですけど、schの方が変わっちゃってる可能性があって、申し訳ないんですけど確認お願いします。
2023-05-27 新モジュールの雛形
2023-05-27 RCSモジュール追加
2023-05-27 一旦保存
2023-05-27 RCS基板を追加
2023-05-27 修正途中
2023-06-07 大変お待たせしました。BatteryPowerV2とINSの改良版です。確認お願いします。
2023-06-07 気圧センサ用ポートを追加
2023-08-16 モジュールの説明を追加
2023-08-18 新LoRaモジュールのファームウェアを追加(WIP)
2023-08-30 Battery Power v2 完成
2023-08-31 ADC DMA修正
2023-08-31 デバッグ用USBシリアルモジュール
2023-09-08 Comm&Logモジュール最新版
2023-09-19 Update GS
